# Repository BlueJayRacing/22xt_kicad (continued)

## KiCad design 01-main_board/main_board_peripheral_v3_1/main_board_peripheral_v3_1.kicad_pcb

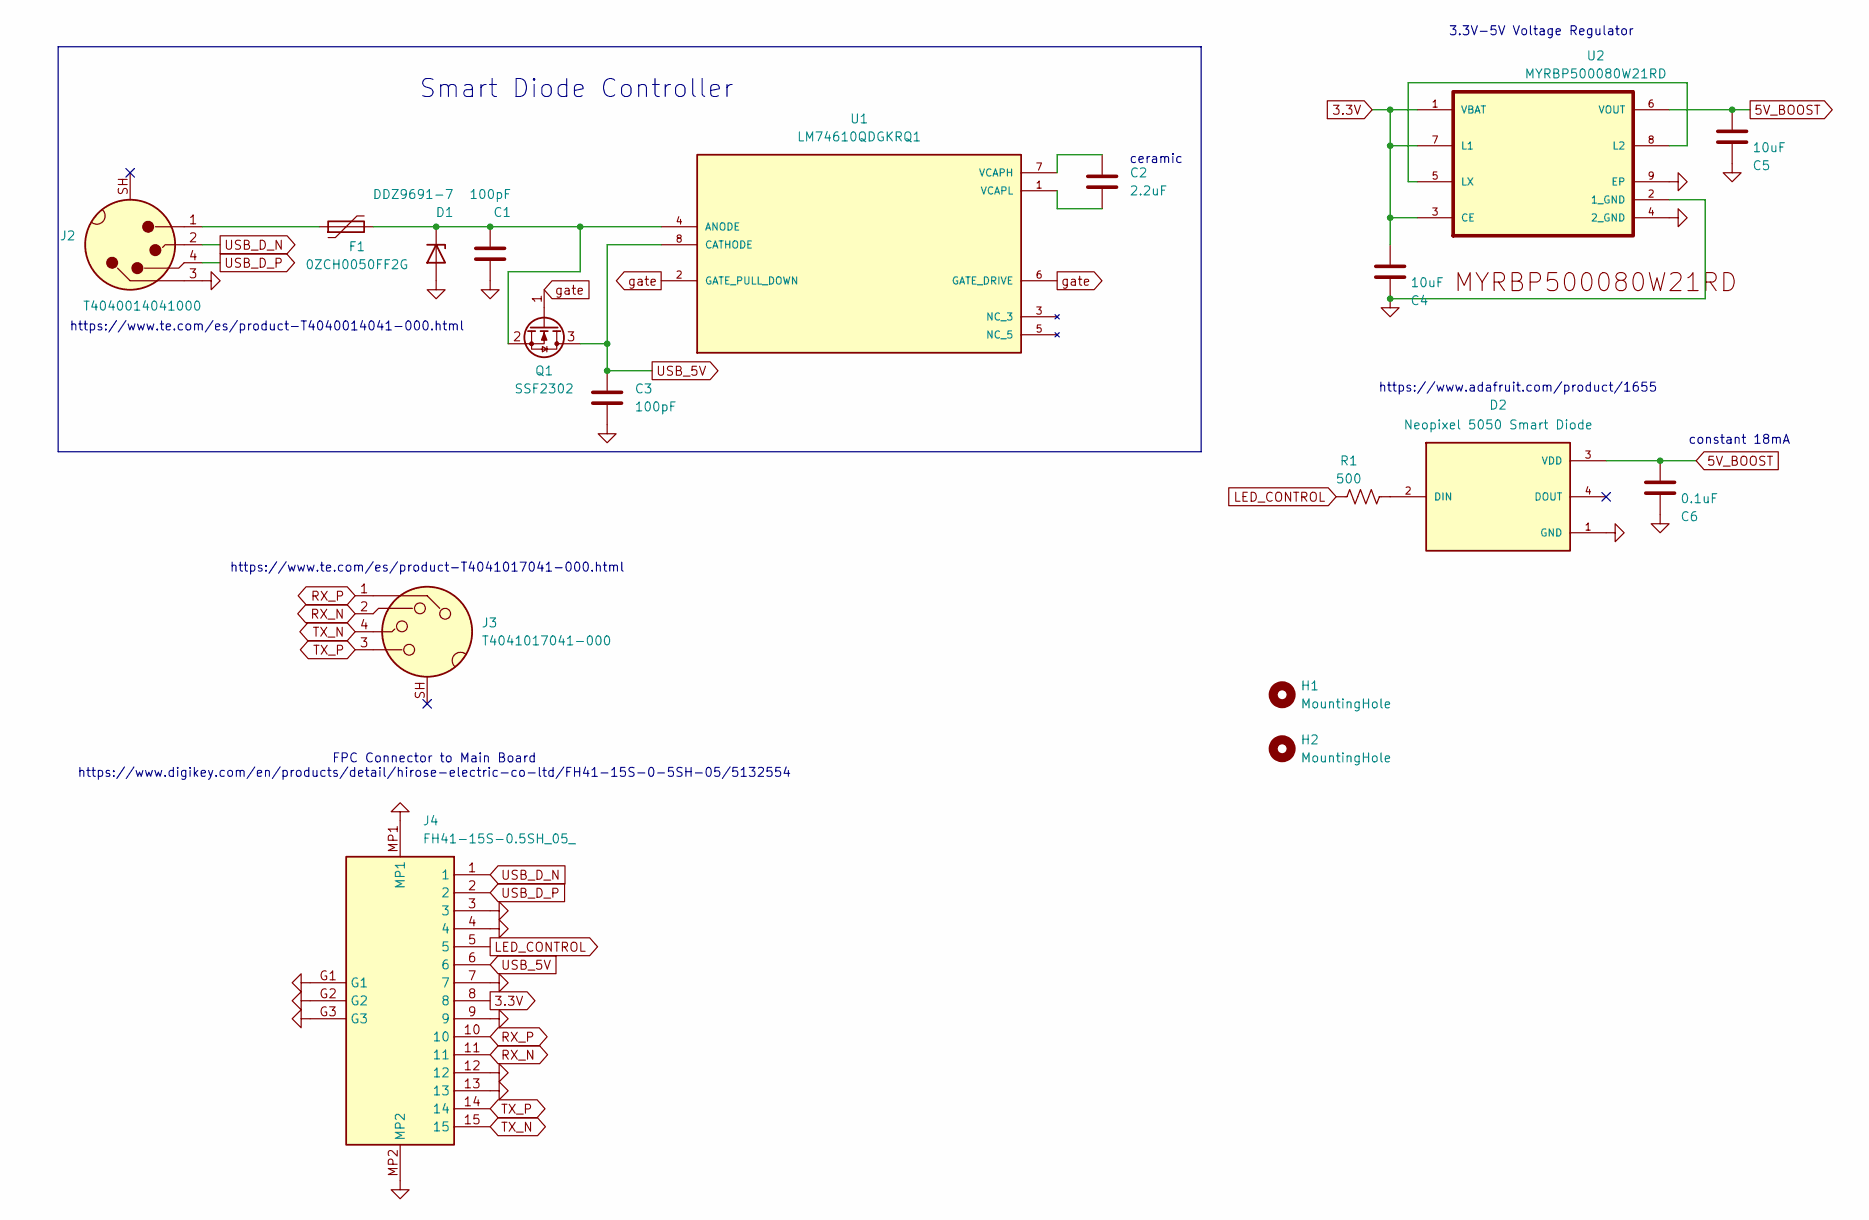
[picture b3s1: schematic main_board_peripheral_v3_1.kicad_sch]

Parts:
C1, C3: 100pF; C_0402_1005Metric
C2: 2.2uF; C_0402_1005Metric
C4, C5: 10uF; C_0603_1608Metric
C6: 0.1uF; C_0402_1005Metric
D1: DDZ9691-7; DDZ9691Q-7
D2: Neopixel 5050 Smart Diode; LED_5050
F1: 0ZCH0050FF2G
H1, H2: MountingHole; ToolingHole_1.152mm
J2: T4040014041000
J3: T4041017041-000; T4041017041000
J4: FH41-15S-0.5SH_05_; FH4115S05SH05; Mouser Part Number 798-FH4115S05SH05
Q1: SSF2302
R1: 500; R_0402_1005Metric
U1: LM74610QDGKRQ1; PARTREV B
U2: MYRBP500080W21RD; MURATA_MYRBP500080W21RD_0; MPN MYRBP500080W21RD

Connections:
3.3V: C4.1, J4.8, U2.1 (VBAT), U2.3 (CE), U2.7 (L1)
5V_BOOST: C5.1, C6.1, D2.3 (VDD), U2.6 (VOUT)
GND: C1.1, C3.2, C4.2, C5.2, C6.2, D1.2 (A), D2.1 (GND), J2.3, J4.3, J4.4, J4.7, J4.9, J4.12, J4.13, J4.G1, J4.G2, J4.G3, J4.MP1, J4.MP2, U2.2 (1_GND), U2.4 (2_GND), U2.9 (EP)
LED_CONTROL: J4.5, R1.1
unnamed: C1.2, D1.1 (K), F1.2, Q1.2 (S), U1.4 (ANODE)
unnamed: D2.2 (DIN), R1.2
unnamed: F1.1, J2.1
unnamed: C2.1, U1.7 (VCAPH)
unnamed: C2.2, U1.1 (VCAPL)
unnamed: U2.5 (LX), U2.8 (L2)
RX_N: J3.2, J4.11
RX_P: J3.1, J4.10
TX_N: J3.4, J4.15
TX_P: J3.3, J4.14
USB_5V: C3.1, J4.6, Q1.3 (D), U1.8 (CATHODE)
USB_D_N: J2.2, J4.1
USB_D_P: J2.4, J4.2
gate: Q1.1 (G), U1.2 (GATE_PULL_DOWN), U1.6 (GATE_DRIVE)

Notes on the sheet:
constant 18mA
3.3V-5V Voltage Regulator
FPC Connector to Main Board https://www.digikey.com/en/products/detail/hirose-electric-co-ltd/FH41-15S-0-5SH-05/5132554
https://www.te.com/es/product-T4041017041-000.html
https://www.adafruit.com/product/1655
ceramic
Smart Diode Controller
https://www.te.com/es/product-T4040014041-000.html

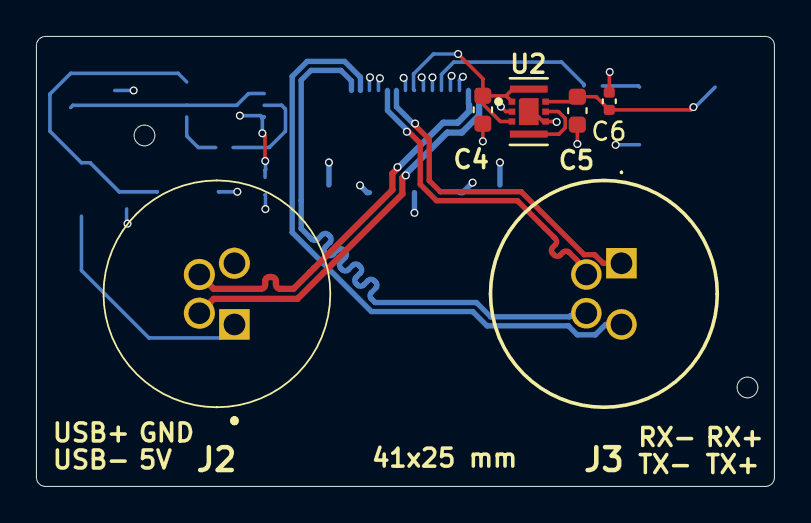
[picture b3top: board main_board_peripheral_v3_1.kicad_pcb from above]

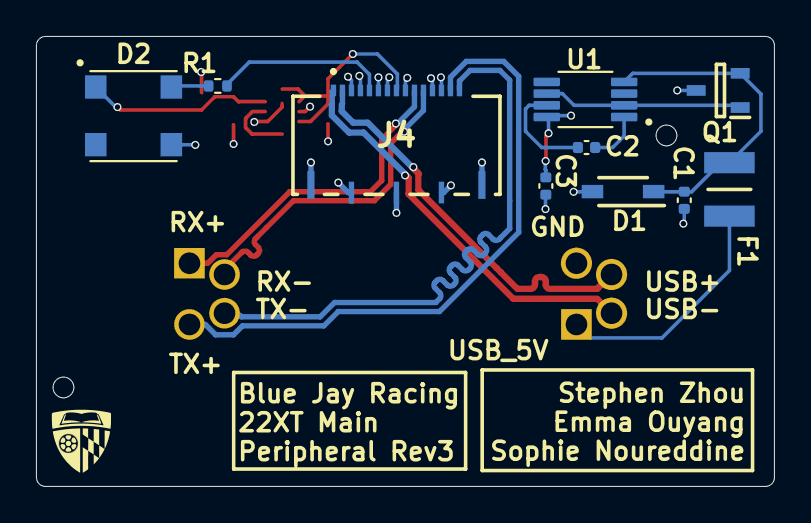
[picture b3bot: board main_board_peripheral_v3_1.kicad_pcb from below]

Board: 4 copper layers, 41.0 x 25.0 mm, 18 parts (10 on the bottom side), 18 nets.

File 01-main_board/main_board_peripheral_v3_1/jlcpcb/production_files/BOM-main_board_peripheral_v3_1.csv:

Comment,Designator,Footprint,LCSC,Quantity
0.1uF,C6,C_0402_1005Metric,C1525,1
100pF,"C1,C3",C_0402_1005Metric,C1546,2
10uF,"C4,C5",C_0603_1608Metric,C19702,2
2.2uF,C2,C_0402_1005Metric,C12530,1
MYRBP500080W21RD,U2,MURATA_MYRBP500080W21RD_0,C6242740,1
T4040014041000,J2,T4040014041000,,1
T4041017041-000,J3,T4041017041000,,1
LM74610QDGKRQ1,U1,LM74610QDGKRQ1,,1
DDZ9691-7,D1,DDZ9691Q-7,,1
FH41-15S-0.5SH_05_,J4,FH4115S05SH05,,1
500,R1,R_0402_1005Metric,,1
0ZCH0050FF2G,F1,0ZCH0050FF2G,,1
SSF2302,Q1,SSF2302,,1
Neopixel 5050 Smart Diode,D2,LED_5050,,1

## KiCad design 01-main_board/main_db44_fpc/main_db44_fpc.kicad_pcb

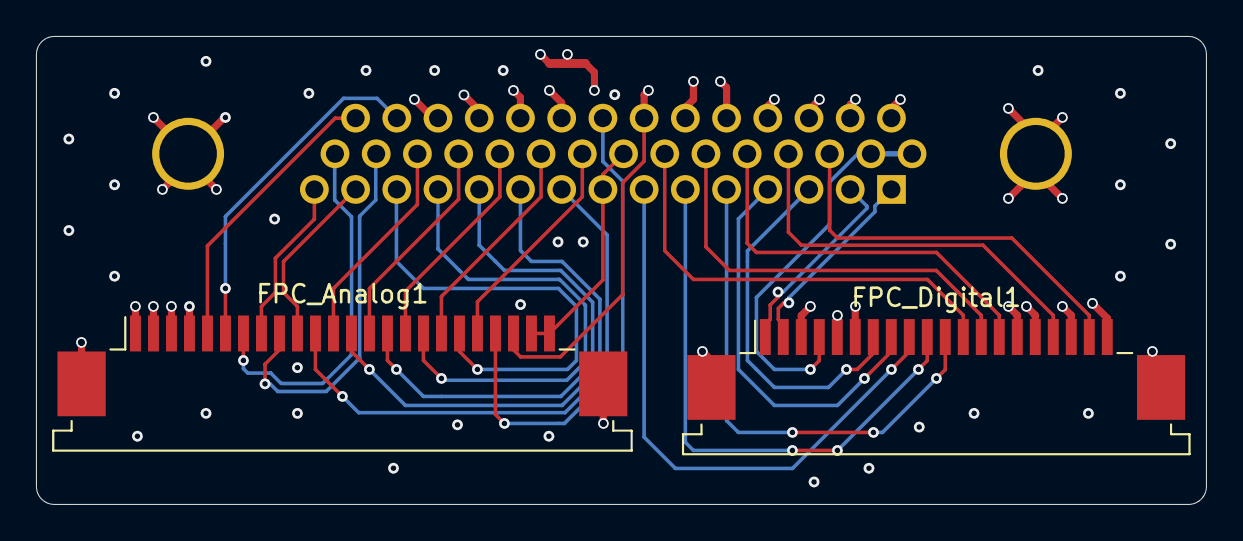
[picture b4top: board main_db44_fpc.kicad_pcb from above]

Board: 4 copper layers, 65.0 x 26.0 mm, 4 parts (1 on the bottom side), 35 nets.

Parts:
FPC_Analog1: Conn_01x24; TE_2-84953-4_1x24-1MP_P1.0mm_Horizontal
FPC_Digital1: Conn_01x20; TE_2-84953-0_1x20-1MP_P1.0mm_Horizontal
J1: DB44_Female; DSUB-44-HD_Socket_Vertical_P2.29x1.98mm_MountingHoles
NT1: NetTie_3_Tee; NetTie-3_SMD_Pad0.5mm

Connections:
3V3 Teensy: FPC_Digital1.4, J1.16, J1.17
5V: FPC_Digital1.5, FPC_Digital1.15, J1.35, J1.36
5V_ref: FPC_Analog1.21, J1.38
11V1: FPC_Analog1.23, FPC_Analog1.24, J1.8, J1.23
AN1: FPC_Analog1.19, J1.13
AN2: FPC_Analog1.17, J1.12
AN3: FPC_Analog1.15, J1.11
AN4: FPC_Analog1.13, J1.10
AN5: FPC_Analog1.11, J1.9
AN6: FPC_Analog1.12, J1.28
AN7: FPC_Analog1.14, J1.27
AN8: FPC_Analog1.16, J1.26
AN9: FPC_Analog1.18, J1.25
AN10: FPC_Analog1.20, J1.24
B-: FPC_Analog1.22, J1.37, NT1.3
CAN +: FPC_Digital1.2, J1.1
CAN -: FPC_Digital1.1, J1.2
D1: FPC_Digital1.9, J1.7
D2: FPC_Digital1.10, J1.6
D3: FPC_Digital1.11, J1.5
D4: FPC_Digital1.12, J1.22
D5: FPC_Digital1.13, J1.21
D6: FPC_Digital1.14, J1.20
GNDA: FPC_Analog1.1, FPC_Analog1.2, FPC_Analog1.3, FPC_Analog1.4, FPC_Analog1.MP, J1.0 (MH), J1.39, J1.40, J1.41, J1.42, NT1.1
GNDD: FPC_Digital1.3, FPC_Digital1.6, FPC_Digital1.16, FPC_Digital1.18, FPC_Digital1.20, FPC_Digital1.MP, J1.0 (MH), J1.31, J1.32, J1.33, J1.34, NT1.2
GP/Int1: FPC_Digital1.17, J1.19
GP/Int2: FPC_Digital1.19, J1.18
I2C_SCL: FPC_Digital1.7, J1.3
I2C_SDA: FPC_Digital1.8, J1.4
sg1_excite: FPC_Analog1.6, J1.43
sg2_excite: FPC_Analog1.5, J1.44
sg_sense_1_FL+: FPC_Analog1.10, J1.14
sg_sense_1_FL-: FPC_Analog1.8, J1.15
sg_sense_2_FR+: FPC_Analog1.9, J1.29
sg_sense_2_FR-: FPC_Analog1.7, J1.30

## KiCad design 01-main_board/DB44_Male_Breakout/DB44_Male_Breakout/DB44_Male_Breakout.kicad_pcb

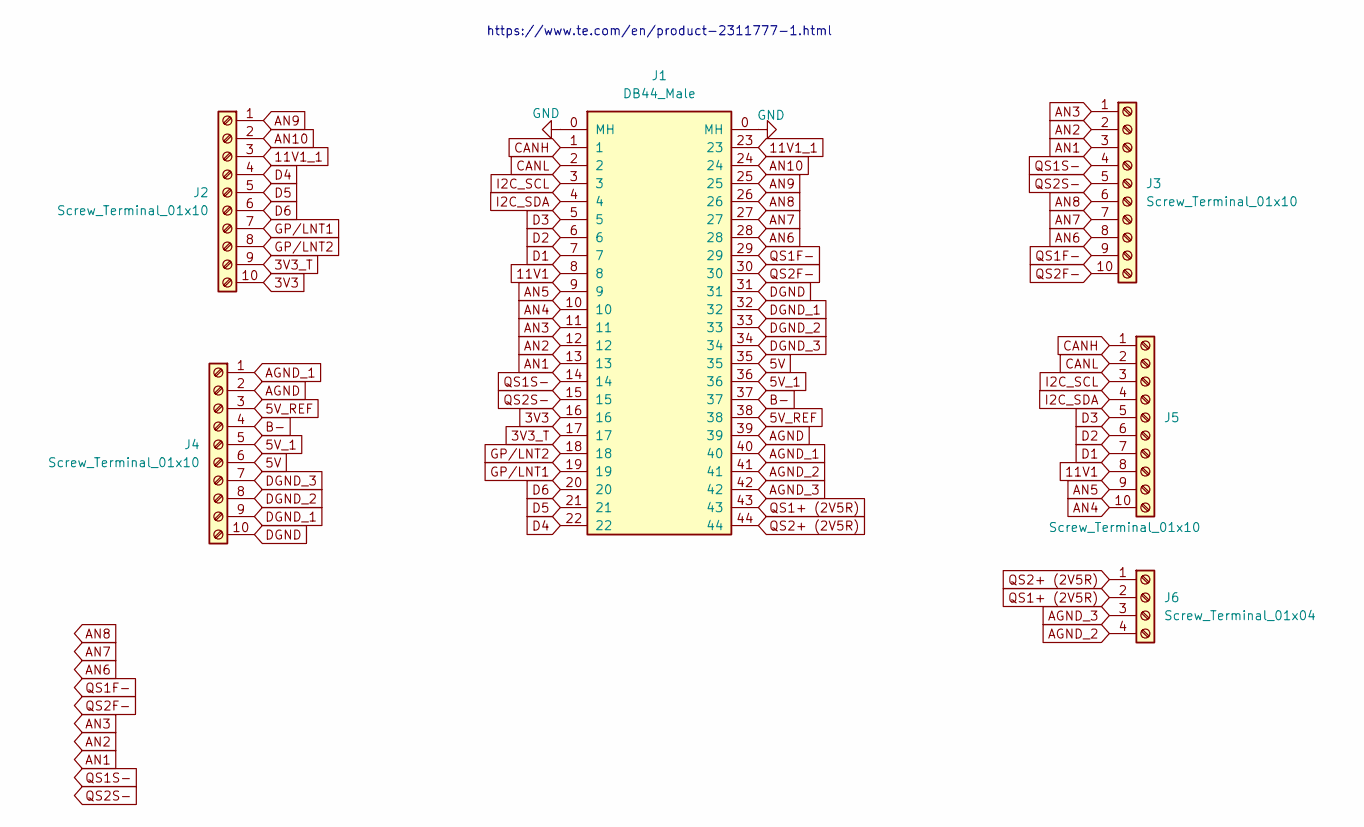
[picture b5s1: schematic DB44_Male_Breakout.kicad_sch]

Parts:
J1: DB44_Male; DSUB-44-HD_Pins_Horizontal_P2.29x2.54mm_EdgePinOffset8.35mm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
J2, J3, J4, J5: Screw_Terminal_01x10; TerminalBlock_RND_205-00240_1x10_P5.08mm_Horizontal
J6: Screw_Terminal_01x04; TerminalBlock_RND_205-00234_1x04_P5.08mm_Horizontal

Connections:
3V3: J1.16, J2.10
3V3_T: J1.17, J2.9
5V: J1.35, J4.6
5V_1: J1.36, J4.5
5V_REF: J1.38, J4.3
11V1: J1.8, J5.8
11V1_1: J1.23, J2.3
AGND: J1.39, J4.2
AGND_1: J1.40, J4.1
AGND_2: J1.41, J6.4
AGND_3: J1.42, J6.3
AN1: J1.13, J3.3
AN2: J1.12, J3.2
AN3: J1.11, J3.1
AN4: J1.10, J5.10
AN5: J1.9, J5.9
AN6: J1.28, J3.8
AN7: J1.27, J3.7
AN8: J1.26, J3.6
AN9: J1.25, J2.1
AN10: J1.24, J2.2
B-: J1.37, J4.4
CANH: J1.1, J5.1
CANL: J1.2, J5.2
D1: J1.7, J5.7
D2: J1.6, J5.6
D3: J1.5, J5.5
D4: J1.22, J2.4
D5: J1.21, J2.5
D6: J1.20, J2.6
DGND: J1.31, J4.10
DGND_1: J1.32, J4.9
DGND_2: J1.33, J4.8
DGND_3: J1.34, J4.7
GND: J1.0 (MH)
GP/LNT1: J1.19, J2.7
GP/LNT2: J1.18, J2.8
I2C_SCL: J1.3, J5.3
I2C_SDA: J1.4, J5.4
QS1+ (2V5R): J1.43, J6.2
QS1F-: J1.29, J3.9
QS1S-: J1.14, J3.4
QS2+ (2V5R): J1.44, J6.1
QS2F-: J1.30, J3.10
QS2S-: J1.15, J3.5

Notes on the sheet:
https://www.te.com/en/product-2311777-1.html

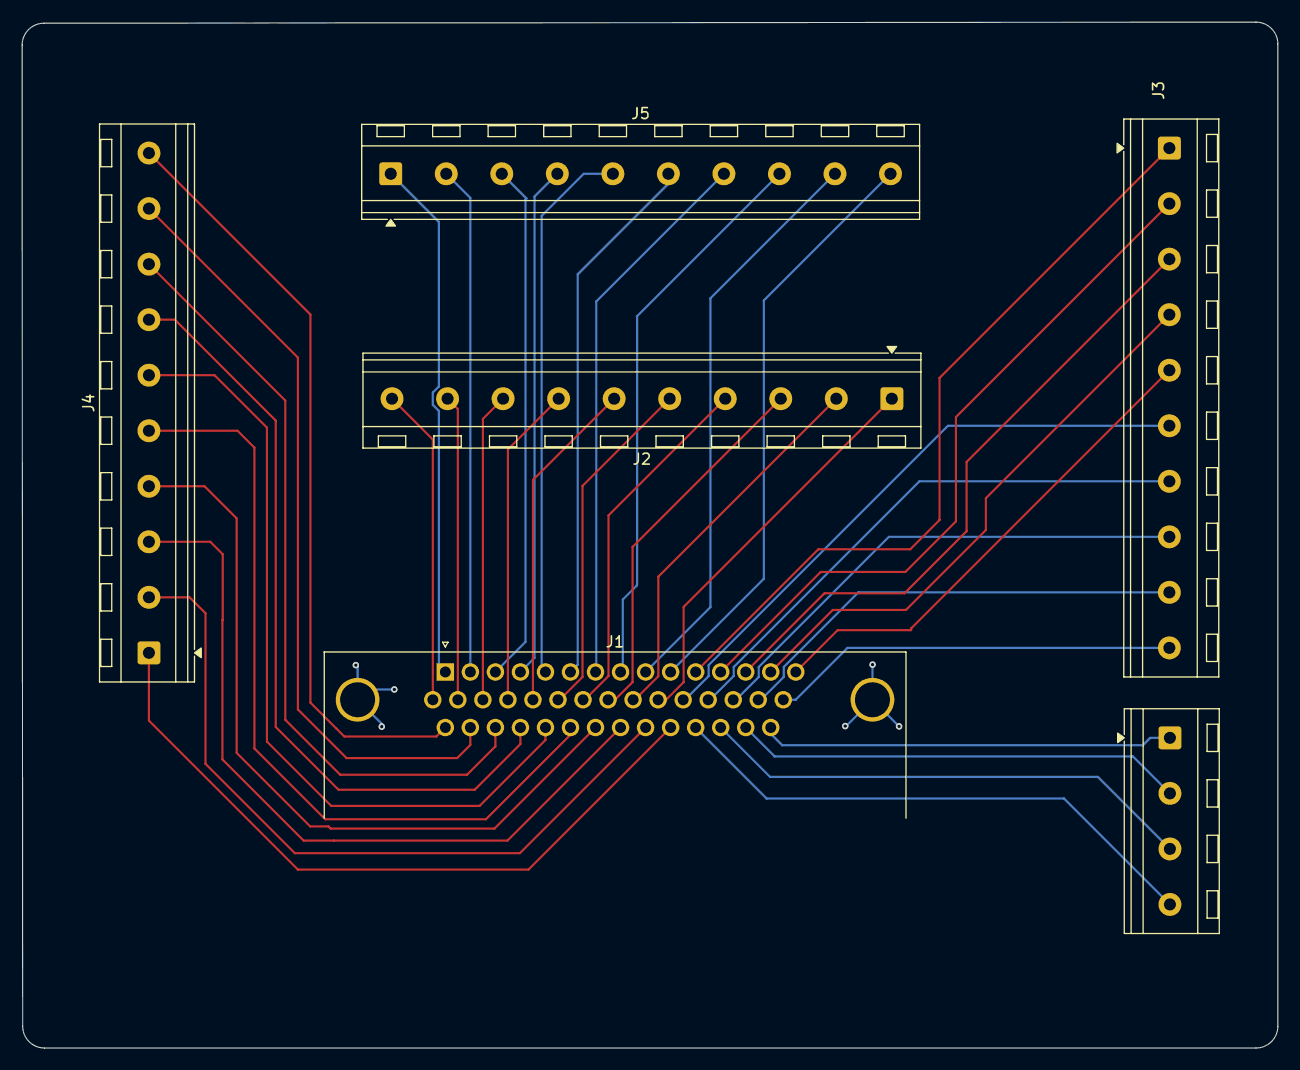
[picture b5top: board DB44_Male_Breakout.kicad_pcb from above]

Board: 2 copper layers, 114.9 x 93.8 mm, 6 parts (0 on the bottom side), 44 nets.

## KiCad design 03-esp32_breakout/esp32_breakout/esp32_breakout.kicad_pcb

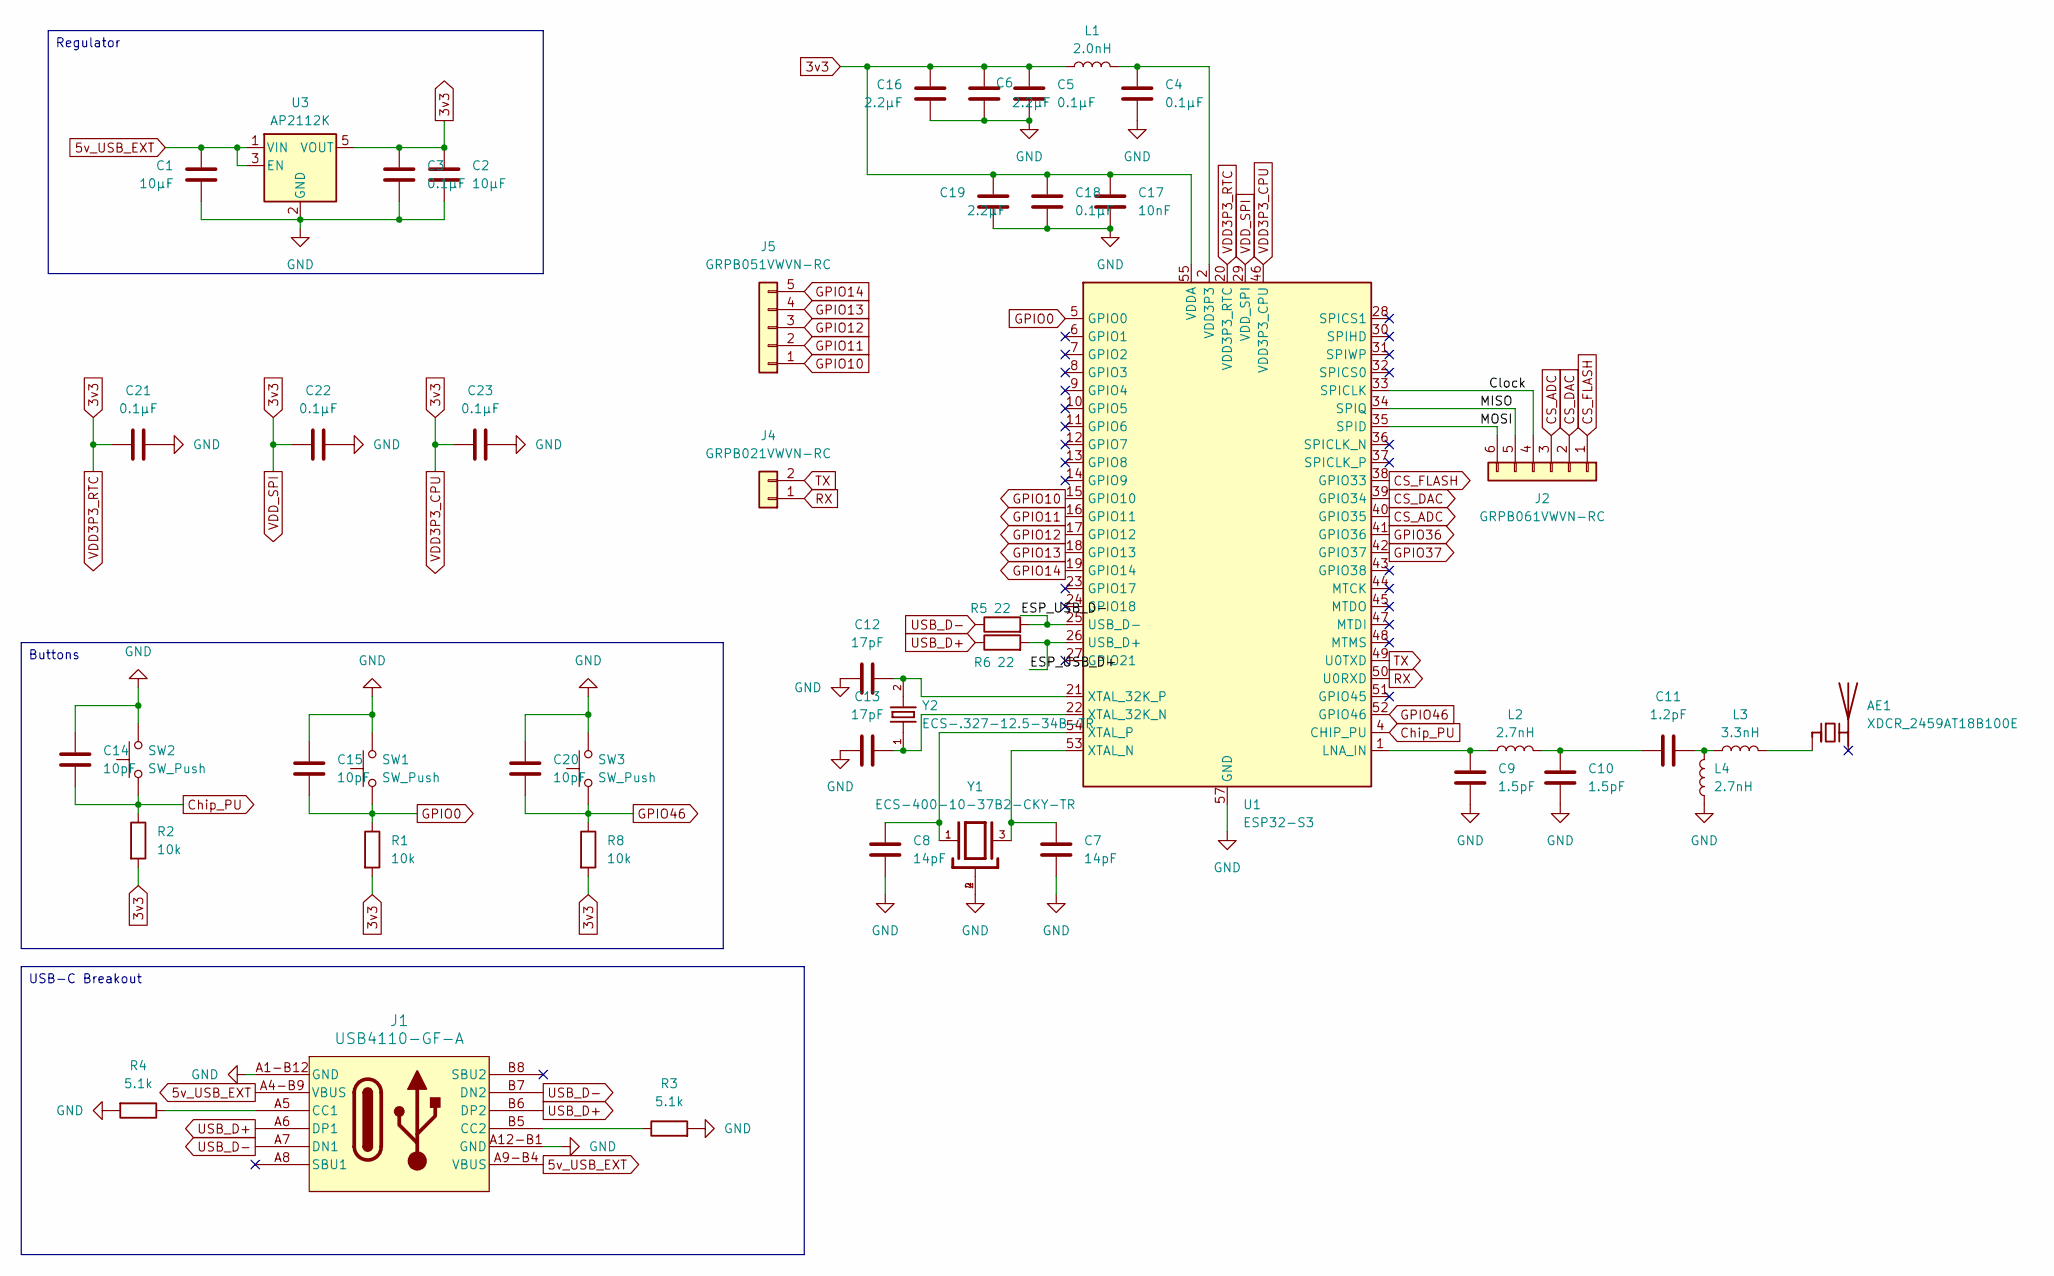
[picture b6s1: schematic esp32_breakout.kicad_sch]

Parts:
AE1: XDCR_2459AT18B100E; XDCR_2450AT18B100E
C1, C2: 10µF; C_0402_1005Metric
C3, C4, C5, C18, C21, C22, C23: 0.1µF; C_0402_1005Metric
C6, C16, C19: 2.2µF; C_0402_1005Metric
C7, C8: 14pF; C_0402_1005Metric
C9, C10: 1.5pF; C_0402_1005Metric
C11: 1.2pF; C_0402_1005Metric
C12, C13: 17pF; C_0402_1005Metric
C14, C15, C20: 10pF; C_0402_1005Metric
C17: 10nF; C_0402_1005Metric
J1: USB4110-GF-A; USB4110-GF-A_GCT
J2: GRPB061VWVN-RC; PinSocket_1x06_P1.27mm_Vertical
J4: GRPB021VWVN-RC; PinSocket_1x02_P1.27mm_Vertical
J5: GRPB051VWVN-RC; PinSocket_1x05_P1.27mm_Vertical
L1: 2.0nH; L_0402_1005Metric
L2, L4: 2.7nH; L_0402_1005Metric
L3: 3.3nH; L_0402_1005Metric
R1, R2, R8: 10k; R_0402_1005Metric
R3, R4: 5.1k; R_0402_1005Metric
R5, R6: 22; R_0402_1005Metric
SW1, SW2, SW3: SW_Push; NANOT100AS_butt
U1: ESP32-S3; QFN-56-1EP_7x7mm_P0.4mm_EP4x4mm
U3: AP2112K; SOT-23-5
Y1: ECS-400-10-37B2-CKY-TR; XTAL_ECS-400-10-37B2-CKY-TR; PARTREV 2021
Y2: ECS-.327-12.5-34B-TR; XTAL_ECS-.327-12.5-34B-TR

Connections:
5v_USB_EXT: C1.2, J1.A4-B9 (VBUS), J1.A9-B4 (VBUS), U3.1 (VIN), U3.3 (EN)
VDD3P3_RTC: C2.2, C3.2, C5.2, C6.2, C16.2, C17.2, C18.2, C19.2, C21.2, C22.2, C23.2, L1.1, R1.2, R2.2, R8.2, U1.20 (VDD3P3_RTC), U1.29 (VDD_SPI), U1.46 (VDD3P3_CPU), U1.55 (VDDA), U1.56 (VDDA), U3.5 (VOUT)
/Clock: J2.4, U1.33 (SPICLK)
/ESP_USB_D+: R6.2, U1.26 (USB_D+)
/ESP_USB_D-: R5.2, U1.25 (USB_D-)
/MISO: J2.5, U1.34 (SPIQ)
/MOSI: J2.6, U1.35 (SPID)
CS_ADC: J2.3, U1.40 (GPIO35)
CS_DAC: J2.2, U1.39 (GPIO34)
CS_FLASH: J2.1, U1.38 (GPIO33)
Chip_PU: C14.1, R2.1, SW2.1, U1.4 (CHIP_PU); also elsewhere on the board
GND: C1.1, C2.1, C3.1, C4.1, C5.1, C6.1, C7.2, C8.1, C9.1, C10.1, C12.1, C13.1, C14.2, C15.2, C16.1, C17.1, C18.1, C19.1, C20.2, C21.1, C22.1, C23.1, J1.A1-B12 (GND), J1.A12-B1 (GND), L4.1, R3.2, R4.2, SW1.2, SW2.2, SW3.2, U1.57 (GND), U3.2 (GND), Y1.2, Y1.4; also elsewhere on the board
GPIO0: C15.1, R1.1, SW1.1, U1.5 (GPIO0); also elsewhere on the board
GPIO10: J5.1, U1.15 (GPIO10)
GPIO11: J5.2, U1.16 (GPIO11)
GPIO12: J5.3, U1.17 (GPIO12)
GPIO13: J5.4, U1.18 (GPIO13)
GPIO14: J5.5, U1.19 (GPIO14)
GPIO36: U1.41 (GPIO36)
GPIO37: U1.42 (GPIO37)
GPIO46: C20.1, R8.1, SW3.1, U1.52 (GPIO46); also elsewhere on the board
unnamed: AE1.1 (FEED), L3.2
unnamed: C4.2, L1.2, U1.2 (VDD3P3), U1.3 (VDD3P3)
unnamed: C10.2, C11.2, L2.2
unnamed: C11.1, L3.1, L4.2
unnamed: J1.A5 (CC1), R4.1
unnamed: J1.B5 (CC2), R3.1
unnamed: C9.2, L2.1, U1.1 (LNA_IN)
unnamed: C13.2, U1.22 (XTAL_32K_N), Y2.1
unnamed: C12.2, U1.21 (XTAL_32K_P), Y2.2
unnamed: C7.1, U1.53 (XTAL_N), Y1.3
unnamed: C8.2, U1.54 (XTAL_P), Y1.1
RX: J4.1, U1.50 (U0RXD)
TX: J4.2, U1.49 (U0TXD)
USB_D+: J1.A6 (DP1), J1.B6 (DP2), R6.1
USB_D-: J1.A7 (DN1), J1.B7 (DN2), R5.1

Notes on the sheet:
USB-C Breakout
Buttons
Regulator

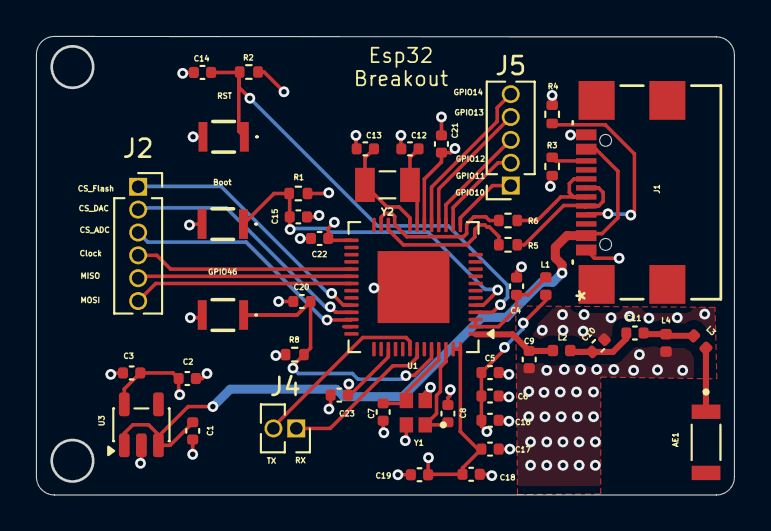
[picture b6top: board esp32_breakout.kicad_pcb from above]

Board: 4 copper layers, 38.8 x 25.5 mm, 46 parts (0 on the bottom side), 34 nets.

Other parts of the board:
Boot: SW_Push; NANOT100AS_butt
GPIO46: SW_Push; NANOT100AS_butt
RST: SW_Push; NANOT100AS_butt

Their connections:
Chip_PU: RST.1; also elsewhere on the board
GND: Boot.2, GPIO46.2, RST.2; also elsewhere on the board
GPIO0: Boot.1; also elsewhere on the board
GPIO46: GPIO46.1; also elsewhere on the board

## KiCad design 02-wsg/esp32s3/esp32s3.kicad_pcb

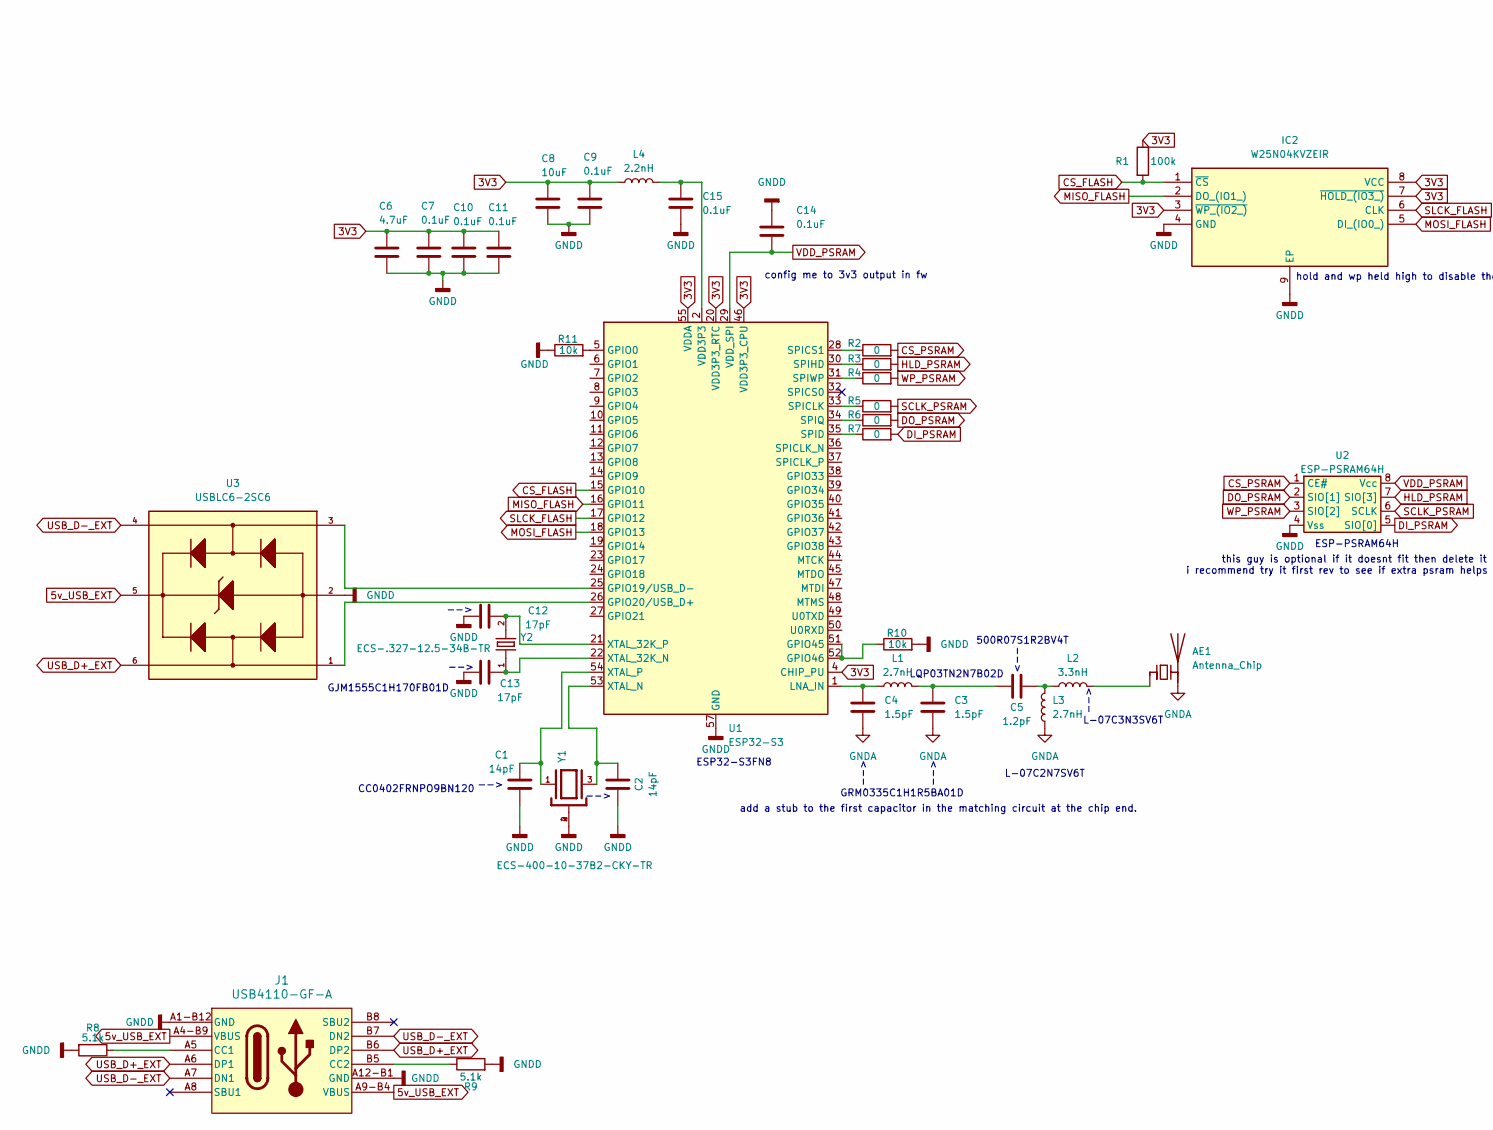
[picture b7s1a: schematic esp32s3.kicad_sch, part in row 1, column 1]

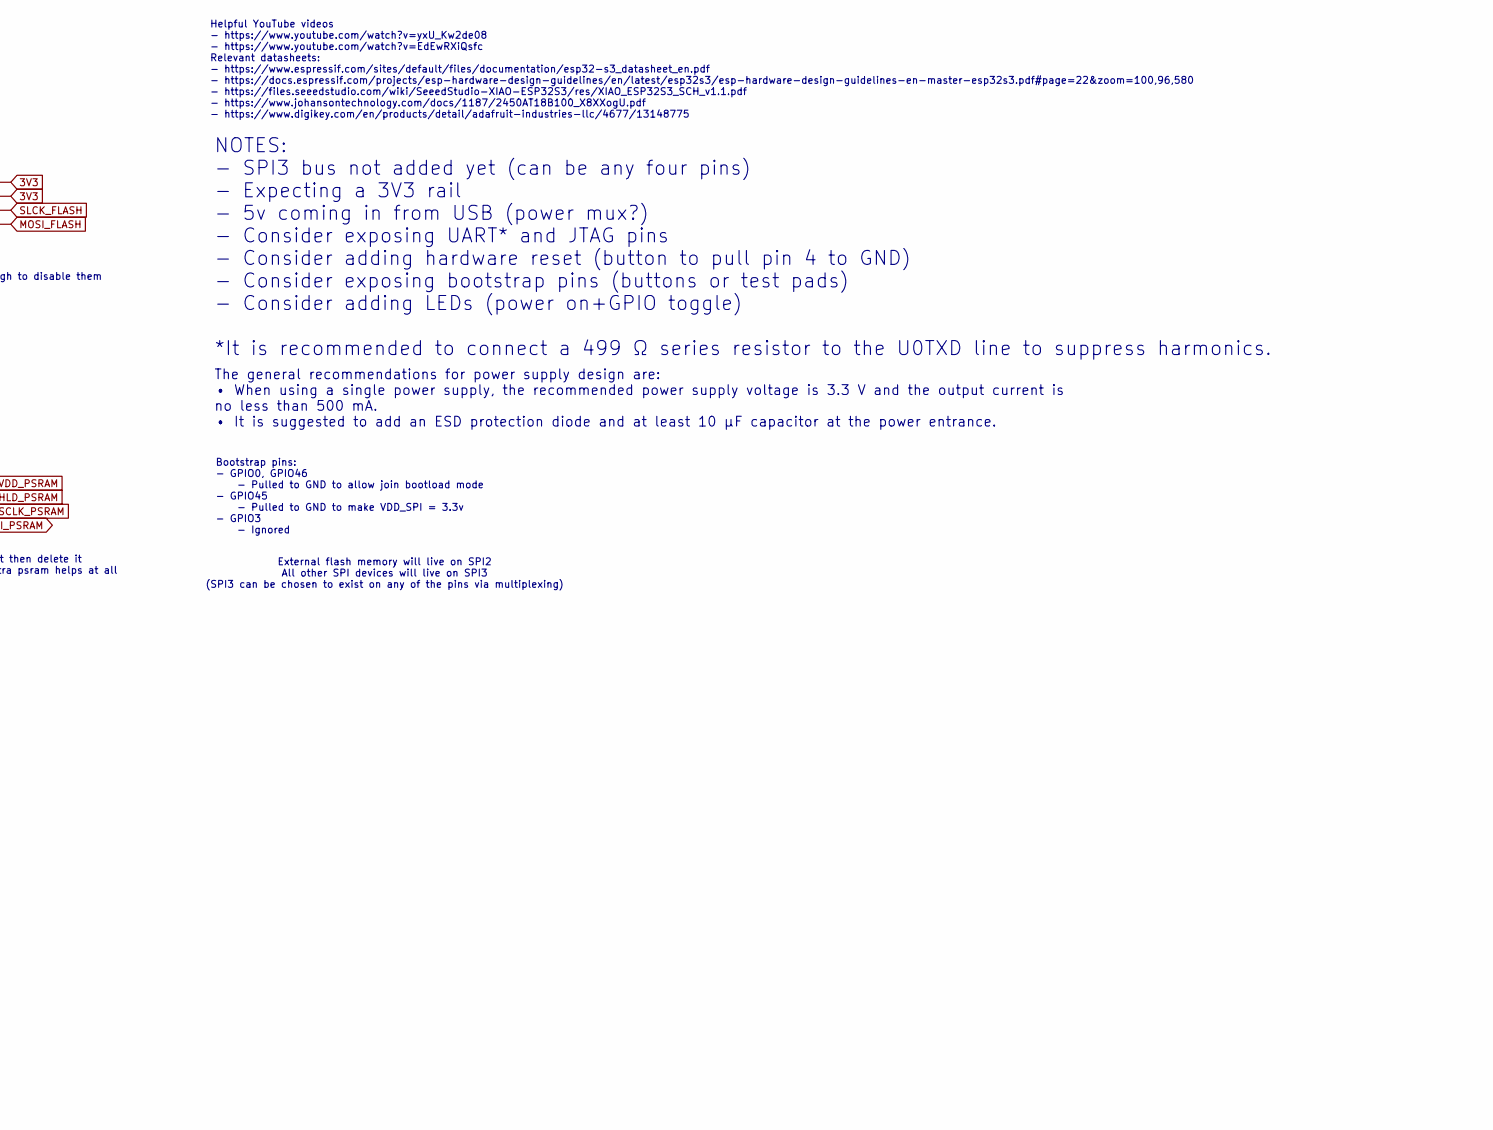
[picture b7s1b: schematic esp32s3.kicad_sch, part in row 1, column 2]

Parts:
AE1: Antenna_Chip; XDCR_2450AT18B100E
C1, C2: 14pF; C_0402_1005Metric
C3, C4: 1.5pF; C_0201_0603Metric
C5: 1.2pF; C_0201_0603Metric
C6: 4.7uF; C_0402_1005Metric
C7, C9, C10, C11, C14, C15: 0.1uF; C_0402_1005Metric
C8: 10uF; C_0402_1005Metric
C12, C13: 17pF; C_0402_1005Metric
IC2: W25N04KVZEIR; SON127P800X600X80-9N-D; Mouser Part Number 454-W25N04KVZEIR
J1: USB4110-GF-A; USB4110-GF-A_GCT
L1: 2.7nH; L_0201_0603Metric
L2: 3.3nH; L_0402_1005Metric
L3: 2.7nH; L_0402_1005Metric
L4: 2.2nH; L_0402_1005Metric
R1: 100k; R_0402_1005Metric
R2, R3, R4, R5, R6, R7: 0; R_0402_1005Metric
R8, R9: 5.1k; R_0402_1005Metric
R10, R11: 10k; R_0402_1005Metric
U1: ESP32-S3; QFN-56-1EP_7x7mm_P0.4mm_EP4x4mm
U2: ESP-PSRAM64H; SOIC-8_3.9x4.9mm_P1.27mm
U3: USBLC6-2SC6; SOT95P280X145-6N
Y1: ECS-400-10-37B2-CKY-TR; XTAL_ECS-400-10-37B2-CKY-TR; PARTREV 2021
Y2: ECS-.327-12.5-34B-TR; XTAL_ECS-.327-12.5-34B-TR

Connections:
3V3: C6.2, C7.2, C8.2, C9.2, C10.2, C11.2, IC2.3 (~WP_(IO2_)), IC2.7 (~HOLD_(IO3_)), IC2.8 (VCC), L4.1, R1.1, U1.4 (CHIP_PU), U1.20 (VDD3P3_RTC), U1.46 (VDD3P3_CPU), U1.55 (VDDA), U1.56 (VDDA)
5v_USB_EXT: J1.A4-B9 (VBUS), J1.A9-B4 (VBUS), U3.5
CS_FLASH: IC2.1 (~CS), R1.2, U1.15 (GPIO10)
CS_PSRAM: R2.2, U2.1 (CE#)
DI_PSRAM: R7.2, U2.5 (SIO[0])
DO_PSRAM: R6.2, U2.2 (SIO[1])
GNDA: AE1.2 (PCB_Trace), C3.1, C4.1, L3.1
GNDD: C1.1, C2.2, C6.1, C7.1, C8.1, C9.1, C10.1, C11.1, C12.1, C13.2, C14.2, C15.1, IC2.4 (GND), IC2.9 (EP), J1.A1-B12 (GND), J1.A12-B1 (GND), R8.2, R9.2, R10.2, R11.1, U1.57 (GND), U2.4 (Vss), U3.2, Y1.2, Y1.4
HLD_PSRAM: R3.2, U2.7 (SIO[3])
MISO_FLASH: IC2.2 (DO_(IO1_)), U1.16 (GPIO11)
MOSI_FLASH: IC2.5 (DI_(IO0_)), U1.18 (GPIO13)
unnamed: AE1.1 (FEED), L2.2
unnamed: C3.2, C5.2, L1.2
unnamed: C5.1, L2.1, L3.2
unnamed: C15.2, L4.2, U1.2 (VDD3P3), U1.3 (VDD3P3)
unnamed: J1.A5 (CC1), R8.1
unnamed: J1.B5 (CC2), R9.1
unnamed: R11.2, U1.5 (GPIO0)
unnamed: U1.25 (GPIO19/USB_D-), U3.3
unnamed: U1.26 (GPIO20/USB_D+), U3.1
unnamed: R10.1, U1.51 (GPIO45), U1.52 (GPIO46)
unnamed: C4.2, L1.1, U1.1 (LNA_IN)
unnamed: R5.1, U1.33 (SPICLK)
unnamed: R2.1, U1.28 (SPICS1)
unnamed: R7.1, U1.35 (SPID)
unnamed: R3.1, U1.30 (SPIHD)
unnamed: R6.1, U1.34 (SPIQ)
unnamed: R4.1, U1.31 (SPIWP)
unnamed: C13.1, U1.22 (XTAL_32K_N), Y2.1
unnamed: C12.2, U1.21 (XTAL_32K_P), Y2.2
unnamed: C2.1, U1.53 (XTAL_N), Y1.3
unnamed: C1.2, U1.54 (XTAL_P), Y1.1
SCLK_PSRAM: R5.2, U2.6 (SCLK)
SLCK_FLASH: IC2.6 (CLK), U1.17 (GPIO12)
USB_D+_EXT: J1.A6 (DP1), J1.B6 (DP2), U3.6
USB_D-_EXT: J1.A7 (DN1), J1.B7 (DN2), U3.4
VDD_PSRAM: C14.1, U1.29 (VDD_SPI), U2.8 (Vcc)
WP_PSRAM: R4.2, U2.3 (SIO[2])

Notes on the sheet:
Helpful YouTube videos - https://www.youtube.com/watch?v=yxU_Kw2de08 - https://www.youtube.com/watch?v=EdEwRXiQsfc Relevant datasheets: - https://www.espressif.com/sites/default/files/documentation/esp32-s3_datasheet_en.pdf - https://docs.espressif.com/projects/esp-hardware-design-guidelines/en/lat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
this guy is optional if it doesnt fit then delete it i recommend try it first rev to see if extra psram helps at all
-->
hold and wp held high to disable them
NOTES: - SPI3 bus not added yet (can be any four pins) - Expecting a 3V3 rail - 5v coming in from USB (power mux?) - Consider exposing UART* and JTAG pins - Consider adding hardware reset (button to pull pin 4 to GND) - Consider exposing bootstrap pins (buttons or test pads) - Consider adding LEDs 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
L-07C2N7SV6T
config me to 3v3 output in fw
add a stub to the first capacitor in the matching circuit at the chip end.
ESP-PSRAM64H
The general recommendations for power supply design are: • When using a single power supply, the recommended power supply voltage is 3.3 V and the output current is no less than 500 mA. • It is suggested to add an ESD protection diode and at least 10 μF capacitor at the power entrance.
500R07S1R2BV4T
L-07C3N3SV6T
External flash memory will live on SPI2 All other SPI devices will live on SPI3 (SPI3 can be chosen to exist on any of the pins via multiplexing)
LQP03TN2N7B02D
GJM1555C1H170FB01D
ESP32-S3FN8
CC0402FRNPO9BN120
<--
Bootstrap pins: - GPIO0, GPIO46 - Pulled to GND to allow join bootload mode - GPIO45 - Pulled to GND to make VDD_SPI = 3.3v - GPIO3 - Ignored
GRM0335C1H1R5BA01D

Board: 2 copper layers, 38 parts (0 on the bottom side), 38 nets, no tracks yet.

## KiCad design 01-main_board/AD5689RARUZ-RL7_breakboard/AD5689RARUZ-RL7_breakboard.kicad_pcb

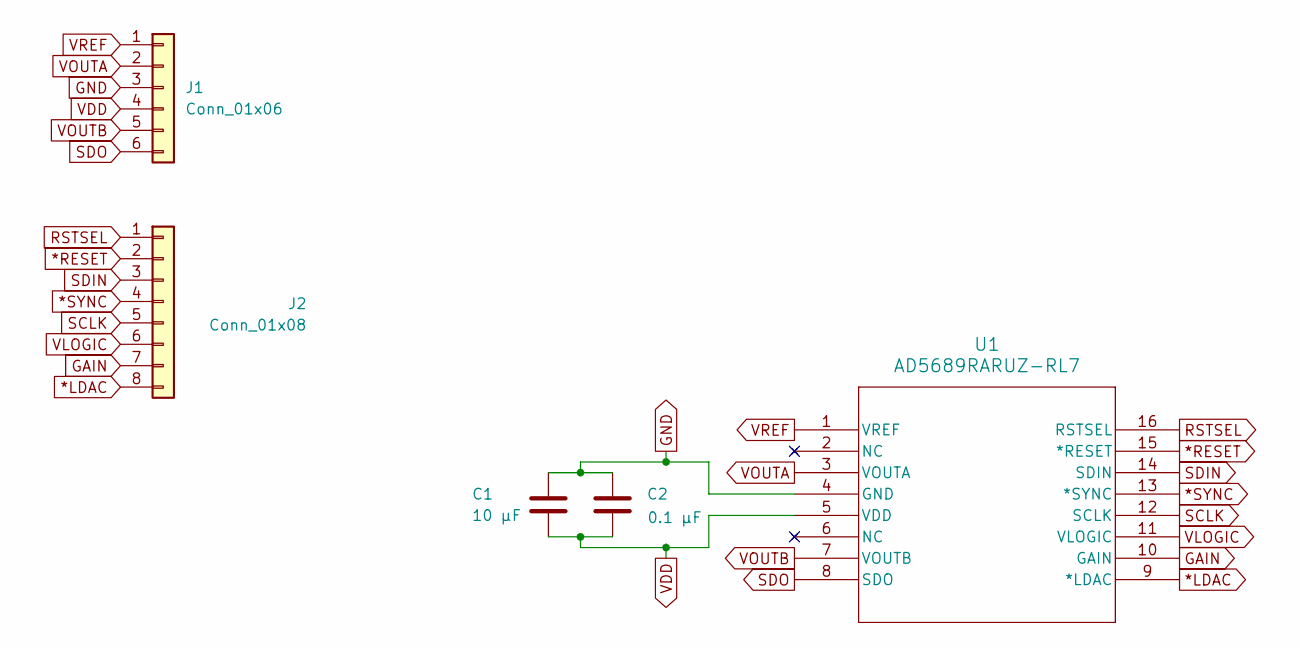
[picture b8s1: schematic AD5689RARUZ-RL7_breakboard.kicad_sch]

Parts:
C1: 10 μF; C_0603_1608Metric
C2: 0.1 μF; C_0201_0603Metric
J1: Conn_01x06; PinHeader_1x06_P2.54mm_Vertical
J2: Conn_01x08; PinHeader_1x08_P2.54mm_Vertical
U1: AD5689RARUZ-RL7; RU_16_ADI

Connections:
*LDAC: J2.8, U1.9 (*LDAC)
*RESET: J2.2, U1.15 (*RESET)
*SYNC: J2.4, U1.13 (*SYNC)
GAIN: J2.7, U1.10 (GAIN)
GND: C1.2, C2.2, J1.3, U1.4 (GND)
RSTSEL: J2.1, U1.16 (RSTSEL)
SCLK: J2.5, U1.12 (SCLK)
SDIN: J2.3, U1.14 (SDIN)
SDO: J1.6, U1.8 (SDO)
VDD: C1.1, C2.1, J1.4, U1.5 (VDD)
VLOGIC: J2.6, U1.11 (VLOGIC)
VOUTA: J1.2, U1.3 (VOUTA)
VOUTB: J1.5, U1.7 (VOUTB)
VREF: J1.1, U1.1 (VREF)

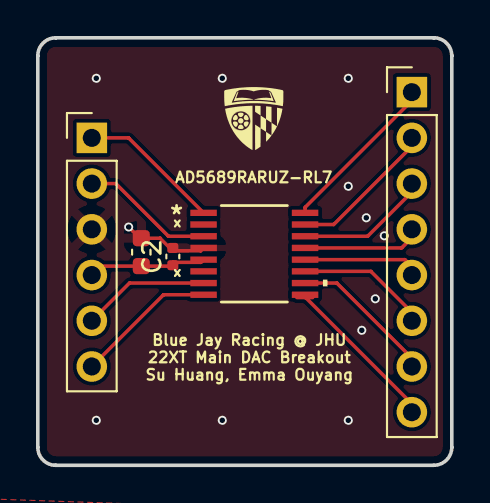
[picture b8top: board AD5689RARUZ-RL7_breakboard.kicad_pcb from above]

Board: 2 copper layers, 23.0 x 23.8 mm, 5 parts (0 on the bottom side), 14 nets.
